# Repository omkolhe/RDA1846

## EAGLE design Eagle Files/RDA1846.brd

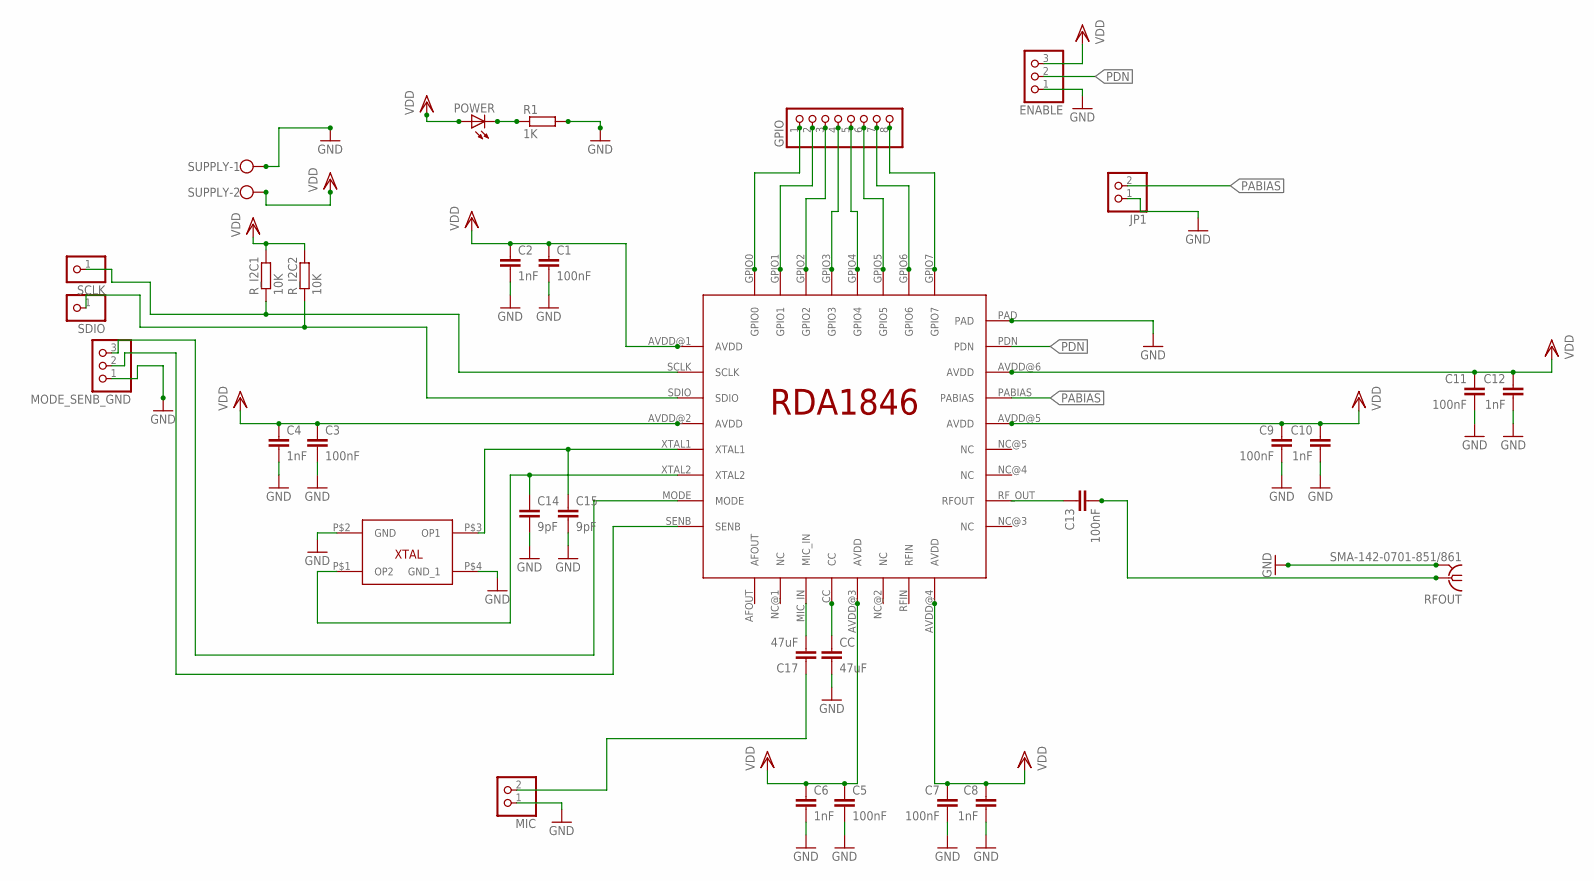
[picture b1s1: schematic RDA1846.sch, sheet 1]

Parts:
C1, C3, C5, C7, C9, C11, C13: 100nF; C0805
C2, C4, C6, C8, C10, C12: 1nF; C0805
C14, C15: 9pF; C0805
C17: 47uF; C0805
CC: 47uF; C0805
ENABLE: PINHD-1X3; 1X03
GPIO: PINHD-1X8CLEANBIG; 1X08-CLEANBIG
JP1: PINHD-1X2; 1X02
MIC: PINHD-1X2; 1X02
MODE_SENB_GND: PINHD-1X3; 1X03
POWER: LEDCHIPLED_1206; CHIPLED_1206
R1: 1K; R0805
RFOUT: SMA-142-0701-851/861; J502-ND-142-0701-851/861
R_I2C1, R_I2C2: 10K; R0805
SCLK: PINHD-1X1; 1X01
SDIO: PINHD-1X1; 1X01
SUPPLY: W237-102
U$1: RDA1846; 32_PIN_QFN
U$2: CRYSTAL_FA_128; FA_128

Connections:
GND: C1.2, C2.2, C3.2, C4.2, C5.2, C6.2, C7.2, C8.2, C9.2, C10.2, C11.2, C12.2, C14.2, C15.2, CC.2, ENABLE.1, JP1.1, MIC.1, MODE_SENB_GND.1, R1.2, RFOUT.G@1 (2), RFOUT.G@2 (2), RFOUT.G@3 (2), RFOUT.G@4 (2), SUPPLY.1, U$1.PAD, U$2.P$2 (GND), U$2.P$4 (GND_1); also elsewhere on the board
MODE: MODE_SENB_GND.3, U$1.MODE
unnamed: GPIO.1, U$1.GPIO0
unnamed: GPIO.8, U$1.GPIO7
unnamed: GPIO.2, U$1.GPIO1
unnamed: GPIO.7, U$1.GPIO6
unnamed: GPIO.3, U$1.GPIO2
unnamed: GPIO.6, U$1.GPIO5
unnamed: GPIO.4, U$1.GPIO3
unnamed: GPIO.5, U$1.GPIO4
unnamed: POWER.C, R1.1
unnamed: CC.1, U$1.CC
unnamed: C13.1, U$1.RF_OUT (RFOUT)
unnamed: C13.2, RFOUT.1
unnamed: C15.1, U$1.XTAL1, U$2.P$3 (OP1)
unnamed: C14.1, U$1.XTAL2, U$2.P$1 (OP2)
unnamed: C17.2, U$1.MIC_IN
unnamed: C17.1, MIC.2
PABIAS: JP1.2, U$1.PABIAS
PDN: ENABLE.2, U$1.PDN
SCLK: R_I2C1.1, SCLK.1, U$1.SCLK
SDIO: R_I2C2.1, SDIO.1, U$1.SDIO
SENB: MODE_SENB_GND.2, U$1.SENB
VDD: C1.1, C2.1, C3.1, C4.1, C5.1, C6.1, C7.1, C8.1, C9.1, C10.1, C11.1, C12.1, ENABLE.3, POWER.A, R_I2C1.2, R_I2C2.2, SUPPLY.2, U$1.AVDD@1 (AVDD), U$1.AVDD@2 (AVDD), U$1.AVDD@3 (AVDD), U$1.AVDD@4 (AVDD), U$1.AVDD@5 (AVDD), U$1.AVDD@6 (AVDD)

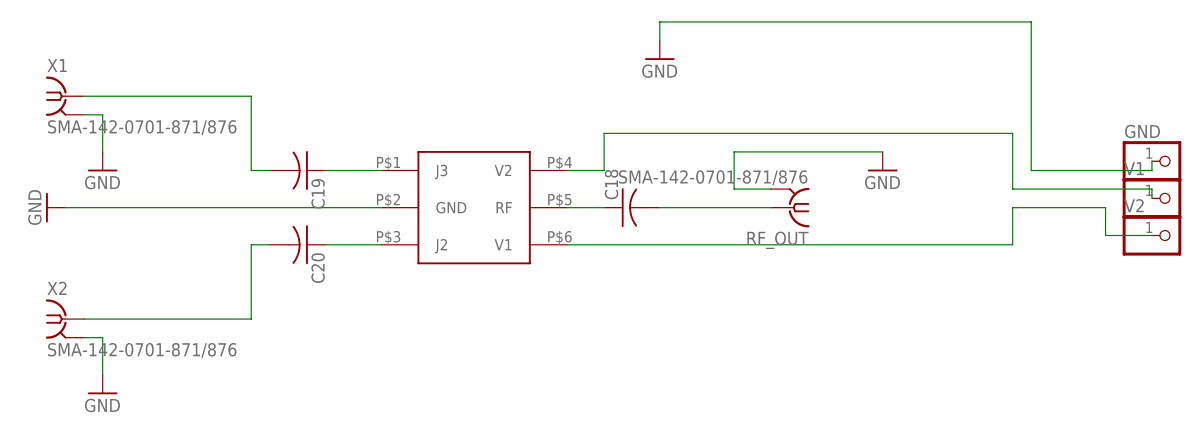
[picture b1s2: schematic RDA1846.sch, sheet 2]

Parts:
C18, C19, C20: C-USC1206; C1206
GND: PINHD-1X1; 1X01
RF_OUT: SMA-142-0701-871/876; J502-ND-142-0701-871/876
U$3: RF_SWITCH; SC90
V1, V2: PINHD-1X1; 1X01
X1, X2: SMA-142-0701-871/876; J502-ND-142-0701-871/876

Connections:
GND: GND.1, RF_OUT.G@1 (2), RF_OUT.G@2 (2), RF_OUT.G@3 (2), RF_OUT.G@4 (2), U$3.P$2 (GND), X1.G@1 (2), X1.G@2 (2), X1.G@3 (2), X1.G@4 (2), X2.G@1 (2), X2.G@2 (2), X2.G@3 (2), X2.G@4 (2); also elsewhere on the board
unnamed: C19.2, X1.1
unnamed: C19.1, U$3.P$1 (J3)
unnamed: C20.1, U$3.P$3 (J2)
unnamed: C20.2, X2.1
unnamed: C18.1, U$3.P$5 (RF)
unnamed: C18.2, RF_OUT.1
unnamed: U$3.P$4 (V2), V1.1
unnamed: U$3.P$6 (V1), V2.1

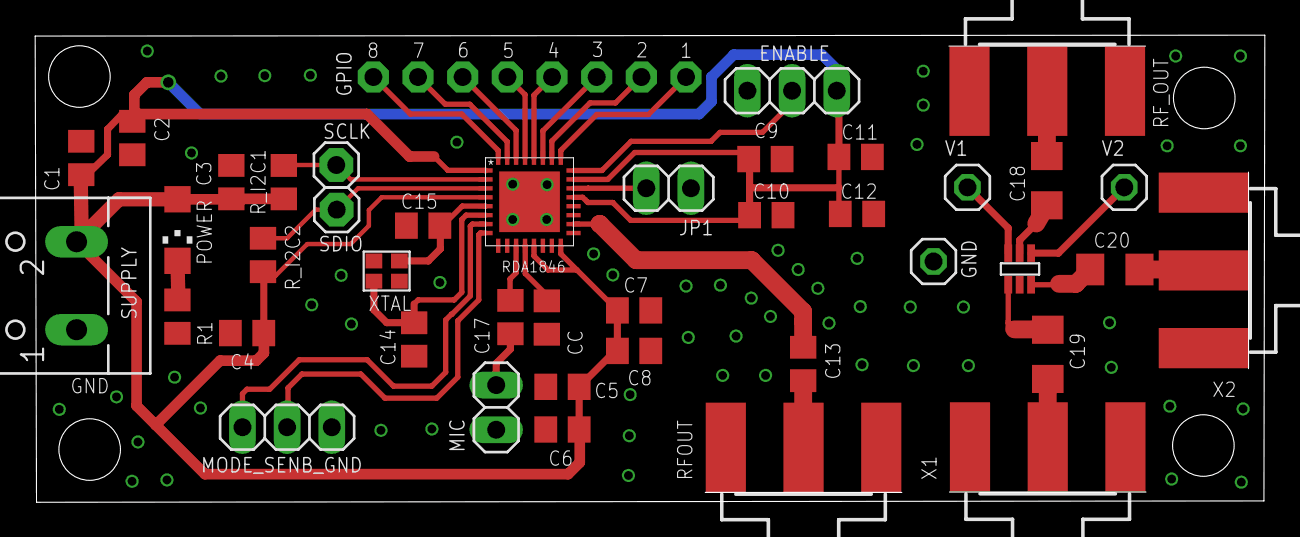
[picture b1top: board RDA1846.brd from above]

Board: 2 copper layers, 69.9 x 26.6 mm, 42 parts (0 on the bottom side), 32 nets.

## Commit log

2018-03-31 Created RDA1846 eagle library. WIP:schematic
2018-08-03 Added FA-128 XTAL Library. WIP : Schematic
2018-08-06 Schematics done. Layout WIP. Check RF Switch dimensions
2018-08-07 Placing of component done. Removed demod spec due to size constraints
2018-08-07 Layout RDA almost done. VCC lines remaining
2018-08-08 Completed layout and routing. Need to adjust labels and values
2018-08-09 Placed all the names and values. QA remaining
2018-08-15 Added mounting holes and values of resisters and capacitors
